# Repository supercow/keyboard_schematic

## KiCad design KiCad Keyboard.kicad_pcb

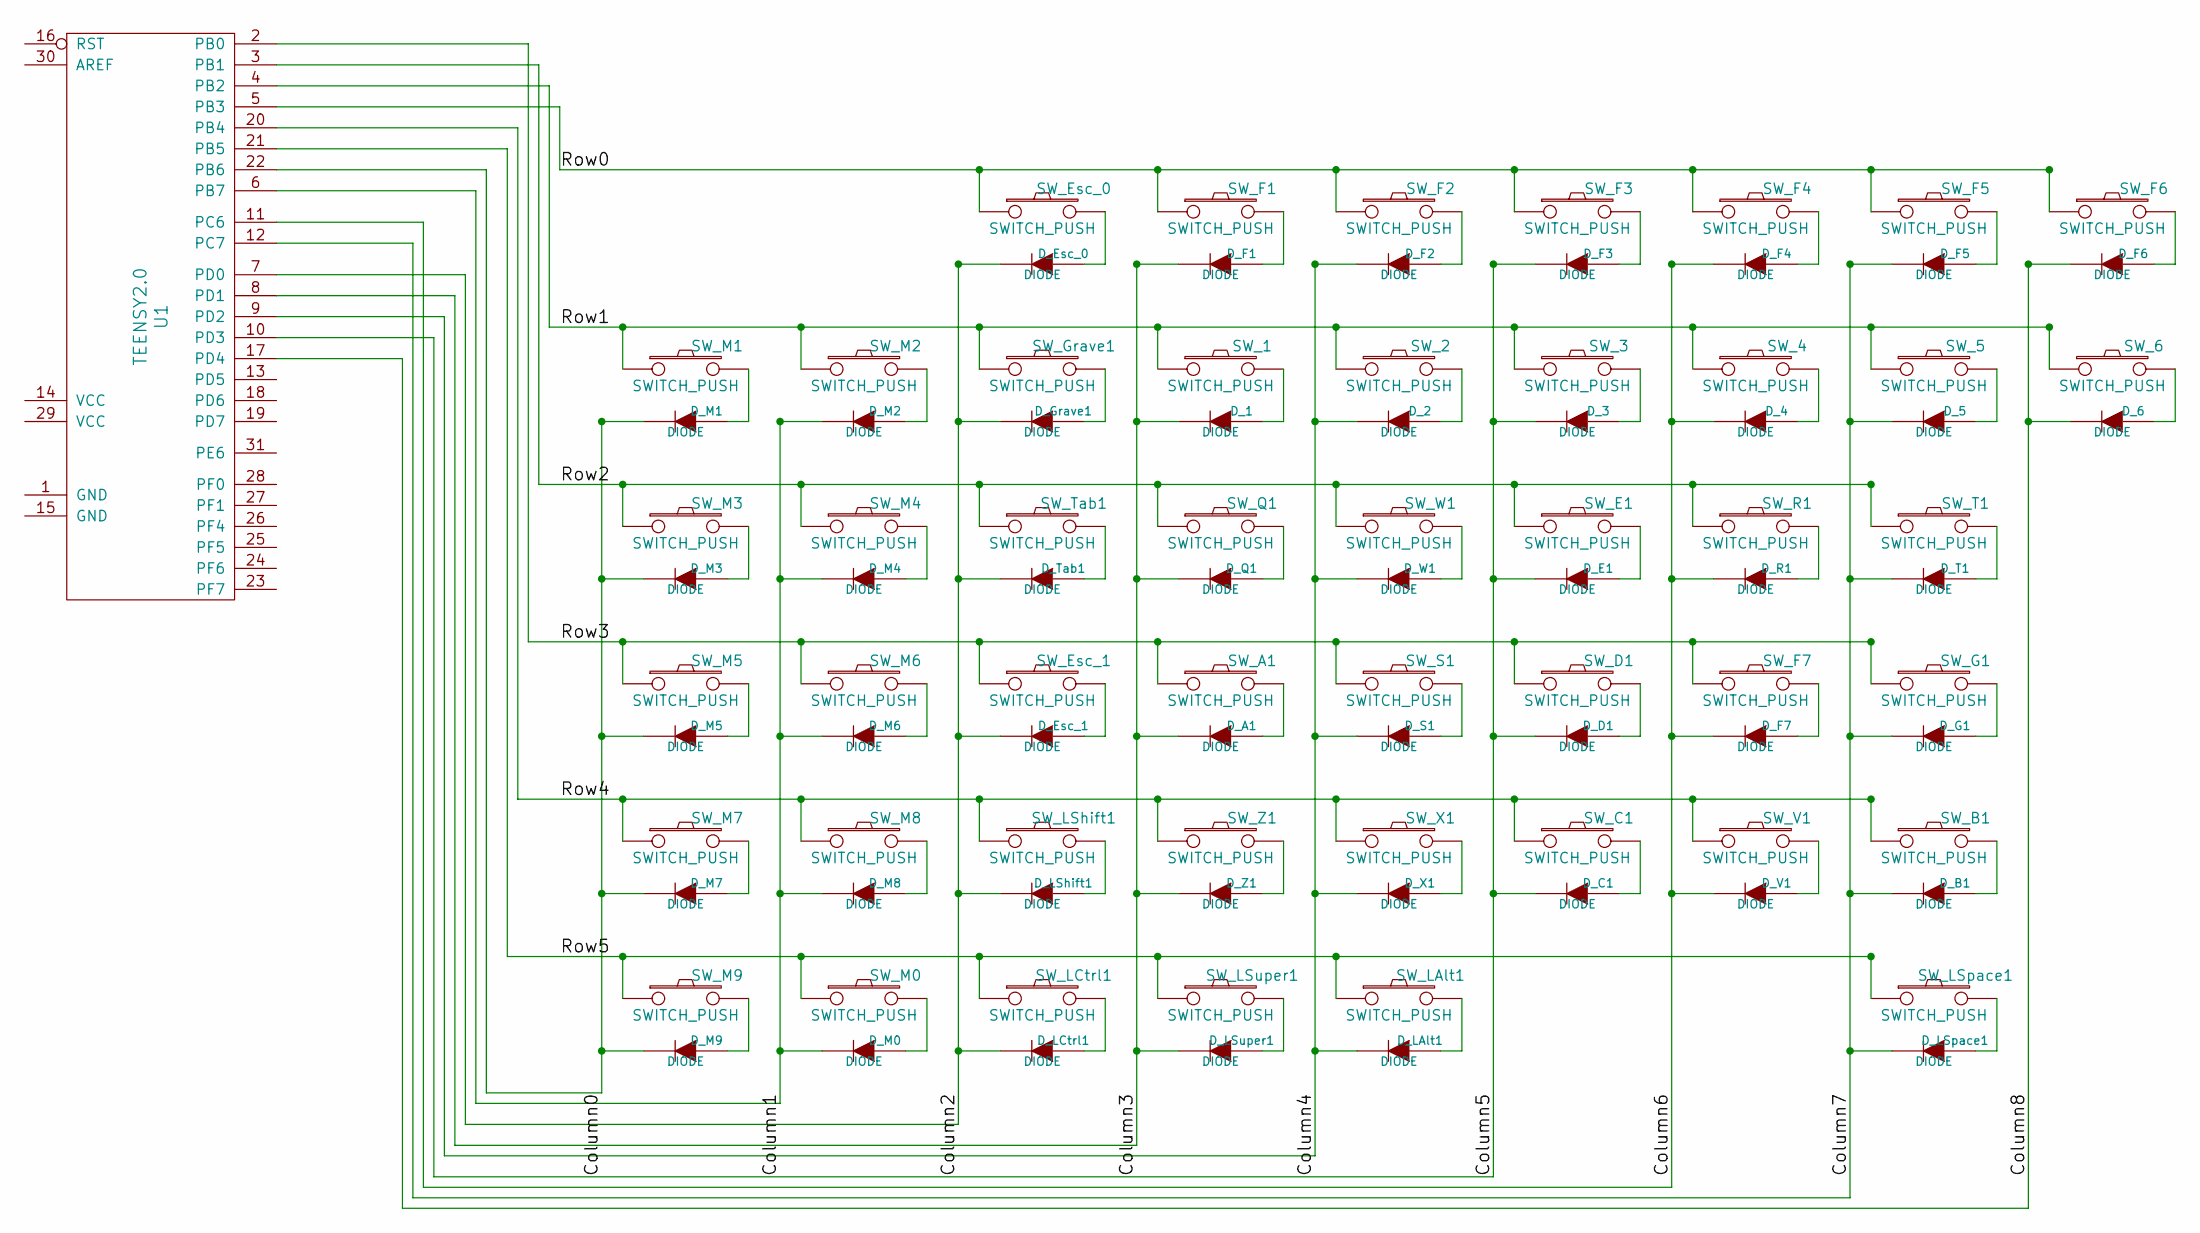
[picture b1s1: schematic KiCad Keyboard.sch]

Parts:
D_1, D_2, D_3, D_4, D_5, D_6: DIODE; CHERRY_MX_DIODE
D_A1: DIODE; CHERRY_MX_DIODE
D_B1: DIODE; CHERRY_MX_DIODE
D_C1: DIODE; CHERRY_MX_DIODE
D_D1: DIODE; CHERRY_MX_DIODE
D_E1: DIODE; CHERRY_MX_DIODE
D_Esc_0, D_Esc_1: DIODE; CHERRY_MX_DIODE
D_F1, D_F2, D_F3, D_F4, D_F5, D_F6, D_F7: DIODE; CHERRY_MX_DIODE
D_G1: DIODE; CHERRY_MX_DIODE
D_Grave1: DIODE; CHERRY_MX_DIODE
D_LAlt1: DIODE; CHERRY_MX_DIODE
D_LCtrl1: DIODE; CHERRY_MX_DIODE
D_LShift1: DIODE; CHERRY_MX_DIODE
D_LSpace1: DIODE; CHERRY_MX_DIODE
D_LSuper1: DIODE; CHERRY_MX_DIODE
D_M0, D_M1, D_M2, D_M3, D_M4, D_M5, D_M6, D_M7, D_M8, D_M9: DIODE; CHERRY_MX_DIODE
D_Q1: DIODE; CHERRY_MX_DIODE
D_R1: DIODE; CHERRY_MX_DIODE
D_S1: DIODE; CHERRY_MX_DIODE
D_T1: DIODE; CHERRY_MX_DIODE
D_Tab1: DIODE; CHERRY_MX_DIODE
D_V1: DIODE; CHERRY_MX_DIODE
D_W1: DIODE; CHERRY_MX_DIODE
D_X1: DIODE; CHERRY_MX_DIODE
D_Z1: DIODE; CHERRY_MX_DIODE
SW_1, SW_2, SW_3, SW_4, SW_5, SW_6: SWITCH_PUSH; CHERRY_PLATE_100H
SW_A1: SWITCH_PUSH; CHERRY_PLATE_100H
SW_B1: SWITCH_PUSH; CHERRY_PLATE_100H
SW_C1: SWITCH_PUSH; CHERRY_PLATE_100H
SW_D1: SWITCH_PUSH; CHERRY_PLATE_100H
SW_E1: SWITCH_PUSH; CHERRY_PLATE_100H
SW_Esc_0: SWITCH_PUSH; CHERRY_PLATE_100H
SW_Esc_1: SWITCH_PUSH; CHERRY_PCB_175H
SW_F1, SW_F2, SW_F3, SW_F4, SW_F5, SW_F6, SW_F7: SWITCH_PUSH; CHERRY_PLATE_100H
SW_G1: SWITCH_PUSH; CHERRY_PLATE_100H
SW_Grave1: SWITCH_PUSH; CHERRY_PLATE_100H
SW_LAlt1: SWITCH_PUSH; CHERRY_PCB_125H
SW_LCtrl1: SWITCH_PUSH; CHERRY_PCB_125H
SW_LShift1: SWITCH_PUSH; CHERRY_PCB_225H
SW_LSpace1: SWITCH_PUSH; CHERRY_PCB_275H
SW_LSuper1: SWITCH_PUSH; CHERRY_PCB_125H
SW_M0, SW_M1, SW_M2, SW_M3, SW_M4, SW_M5, SW_M6, SW_M7, SW_M8, SW_M9: SWITCH_PUSH; CHERRY_PLATE_100H
SW_Q1: SWITCH_PUSH; CHERRY_PLATE_100H
SW_R1: SWITCH_PUSH; CHERRY_PLATE_100H
SW_S1: SWITCH_PUSH; CHERRY_PLATE_100H
SW_T1: SWITCH_PUSH; CHERRY_PLATE_100H
SW_Tab1: SWITCH_PUSH; CHERRY_PCB_150H
SW_V1: SWITCH_PUSH; CHERRY_PLATE_100H
SW_W1: SWITCH_PUSH; CHERRY_PLATE_100H
SW_X1: SWITCH_PUSH; CHERRY_PLATE_100H
SW_Z1: SWITCH_PUSH; CHERRY_PLATE_100H
U1: TEENSY2.0

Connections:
/Column0: D_M1.2 (K), D_M3.2 (K), D_M5.2 (K), D_M7.2 (K), D_M9.2 (K), U1.22 (PB6)
/Column1: D_M0.2 (K), D_M2.2 (K), D_M4.2 (K), D_M6.2 (K), D_M8.2 (K), U1.6 (PB7)
/Column2: D_Esc_0.2 (K), D_Esc_1.2 (K), D_Grave1.2 (K), D_LCtrl1.2 (K), D_LShift1.2 (K), D_Tab1.2 (K), U1.7 (PD0)
/Column3: D_1.2 (K), D_A1.2 (K), D_F1.2 (K), D_LSuper1.2 (K), D_Q1.2 (K), D_Z1.2 (K), U1.8 (PD1)
/Column4: D_2.2 (K), D_F2.2 (K), D_LAlt1.2 (K), D_S1.2 (K), D_W1.2 (K), D_X1.2 (K), U1.9 (PD2)
/Column5: D_3.2 (K), D_C1.2 (K), D_D1.2 (K), D_E1.2 (K), D_F3.2 (K), U1.10 (PD3)
/Column6: D_4.2 (K), D_F4.2 (K), D_F7.2 (K), D_R1.2 (K), D_V1.2 (K), U1.11 (PC6)
/Column7: D_5.2 (K), D_B1.2 (K), D_F5.2 (K), D_G1.2 (K), D_LSpace1.2 (K), D_T1.2 (K), U1.12 (PC7)
/Column8: D_6.2 (K), D_F6.2 (K), U1.17 (PD4)
/Row0: SW_Esc_0.1, SW_F1.1, SW_F2.1, SW_F3.1, SW_F4.1, SW_F5.1, SW_F6.1, U1.5 (PB3)
/Row1: SW_1.1, SW_2.1, SW_3.1, SW_4.1, SW_5.1, SW_6.1, SW_Grave1.1, SW_M1.1, SW_M2.1, U1.4 (PB2)
/Row2: SW_E1.1, SW_M3.1, SW_M4.1, SW_Q1.1, SW_R1.1, SW_T1.1, SW_Tab1.1, SW_W1.1, U1.3 (PB1)
/Row3: SW_A1.1, SW_D1.1, SW_Esc_1.1, SW_F7.1, SW_G1.1, SW_M5.1, SW_M6.1, SW_S1.1, U1.2 (PB0)
/Row4: SW_B1.1, SW_C1.1, SW_LShift1.1, SW_M7.1, SW_M8.1, SW_V1.1, SW_X1.1, SW_Z1.1, U1.20 (PB4)
/Row5: SW_LAlt1.1, SW_LCtrl1.1, SW_LSpace1.1, SW_LSuper1.1, SW_M0.1, SW_M9.1, U1.21 (PB5)
unnamed: D_1.1 (A), SW_1.2
unnamed: D_2.1 (A), SW_2.2
unnamed: D_3.1 (A), SW_3.2
unnamed: D_4.1 (A), SW_4.2
unnamed: D_5.1 (A), SW_5.2
unnamed: D_6.1 (A), SW_6.2
unnamed: D_A1.1 (A), SW_A1.2
unnamed: D_B1.1 (A), SW_B1.2
unnamed: D_C1.1 (A), SW_C1.2
unnamed: D_D1.1 (A), SW_D1.2
unnamed: D_E1.1 (A), SW_E1.2
unnamed: D_Esc_0.1 (A), SW_Esc_0.2
unnamed: D_Esc_1.1 (A), SW_Esc_1.2
unnamed: D_F1.1 (A), SW_F1.2
unnamed: D_F2.1 (A), SW_F2.2
unnamed: D_F3.1 (A), SW_F3.2
unnamed: D_F4.1 (A), SW_F4.2
unnamed: D_F5.1 (A), SW_F5.2
unnamed: D_F6.1 (A), SW_F6.2
unnamed: D_F7.1 (A), SW_F7.2
unnamed: D_G1.1 (A), SW_G1.2
unnamed: D_Grave1.1 (A), SW_Grave1.2
unnamed: D_LAlt1.1 (A), SW_LAlt1.2
unnamed: D_LCtrl1.1 (A), SW_LCtrl1.2
unnamed: D_LShift1.1 (A), SW_LShift1.2
unnamed: D_LSpace1.1 (A), SW_LSpace1.2
unnamed: D_LSuper1.1 (A), SW_LSuper1.2
unnamed: D_M0.1 (A), SW_M0.2
unnamed: D_M1.1 (A), SW_M1.2
unnamed: D_M2.1 (A), SW_M2.2
unnamed: D_M3.1 (A), SW_M3.2
unnamed: D_M4.1 (A), SW_M4.2
unnamed: D_M5.1 (A), SW_M5.2
unnamed: D_M6.1 (A), SW_M6.2
unnamed: D_M7.1 (A), SW_M7.2
unnamed: D_M8.1 (A), SW_M8.2
unnamed: D_M9.1 (A), SW_M9.2
unnamed: D_Q1.1 (A), SW_Q1.2
unnamed: D_R1.1 (A), SW_R1.2
unnamed: D_S1.1 (A), SW_S1.2
unnamed: D_T1.1 (A), SW_T1.2
unnamed: D_Tab1.1 (A), SW_Tab1.2
unnamed: D_V1.1 (A), SW_V1.2
unnamed: D_W1.1 (A), SW_W1.2
unnamed: D_X1.1 (A), SW_X1.2
unnamed: D_Z1.1 (A), SW_Z1.2

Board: 2 copper layers, 93 parts (0 on the bottom side), 61 nets, no tracks yet.

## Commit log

2017-03-05 Add row/column labels
2017-03-05 Wire row/column to teensy
2017-03-05 First pass on pcb placement
2017-03-05 Stray row label
2017-03-06 Basic keyboard arrangement
2017-03-17 Changing diodes to SMD
